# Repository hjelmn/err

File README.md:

This project contains all the files from my recreation of the Err LED sign. Included
in this repository are the current Kicad files.

The board is roughly based on the data available at:

https://hackaday.io/project/183827-reverse-engineering-the-mooninite-led-panels/details

with minor modifications (there could be errors-- if you find some please post a
PR with the fix):

 - Added a tactile switch to control the mode of the panel. The modes are off,
   light triggered, and various dimmed states but this can be changed by
   modifying the PIC firmware.
 - Added a barrel power input to support an external power supply. Added a
   circuit to disable the batter if an external power supply is connected. This
   circuit uses a P-channel MOSFET which closes the Batt+ when a voltage is
   detected on Vcc.
 - Added a battery pack connector and pads to solder on a battery.
 - Increased the LED driver voltage from 12v to 24v using boost regulator.
 - Changed the 5v regulator to a D2Pak style from the TO-220.
 - Added a 24 channel dimmable LED driver and rewired LEDs in chains of 6-8.
 - Changed to PIC16 to get I2C support but that is not needed with the LED
   controller chosen. It uses PWR so the originsl PIC12 is likely sufficient.

TODO:

 - Code for the microcontroller. Waiting on getting the parts before the code is
   finished.

The current version of the board costs roughly $85 to produce with LEDs from
China and parts sourced from the US.

To use this project download kicad and open the project.

The license for all of these files is GPLv3.

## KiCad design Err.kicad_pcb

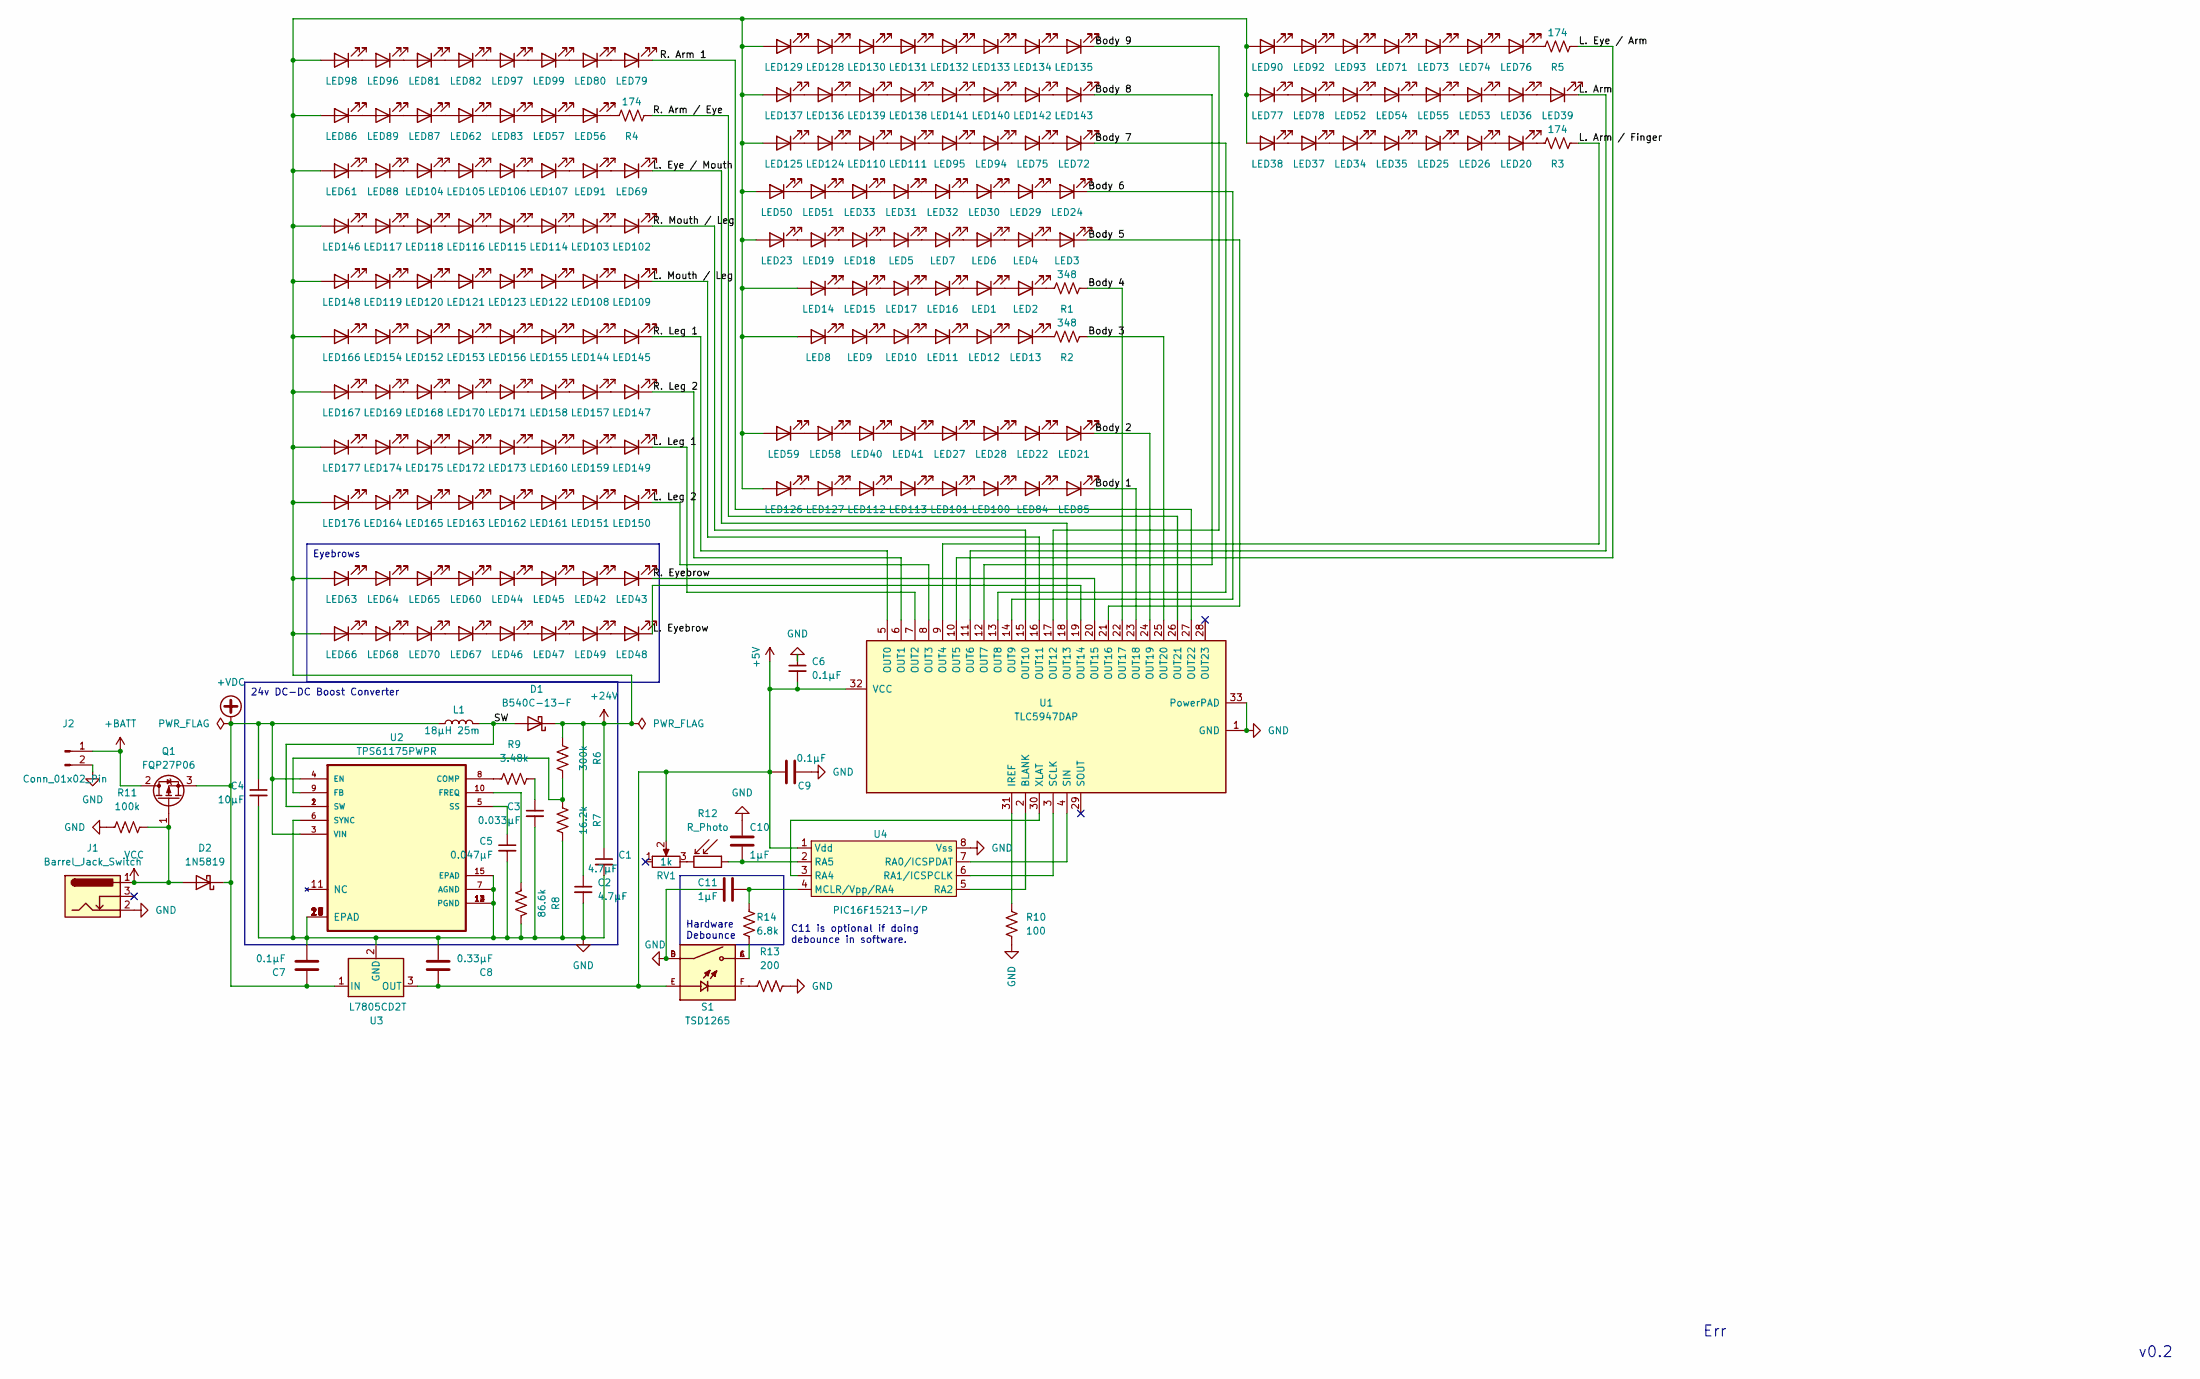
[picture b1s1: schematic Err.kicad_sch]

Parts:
C1, C2: 4.7µF; C_1206_3216Metric_Pad1.33x1.80mm_HandSolder; Part GRM31CR71H475KA12L
C3: 0.033µF; C_0805_2012Metric_Pad1.18x1.45mm_HandSolder; Part CGA4J2C0G1H333J125AA
C4: 10µF; C_1206_3216Metric_Pad1.33x1.80mm_HandSolder; Part GRM31CR71E106KA12L
C5: 0.047µF; C_0805_2012Metric_Pad1.18x1.45mm_HandSolder; Part C0805C473J3GACTU
C6: 0.1µF; C_0805_2012Metric_Pad1.18x1.45mm_HandSolder; Part GRM31CR71H475KA12L
C7, C9: 0.1µF; C_Disc_D3.0mm_W2.0mm_P2.50mm; Part C320C104K5R5TA
C8: 0.33µF; C_Disc_D5.1mm_W3.2mm_P5.00mm; Part SR215E334MAATR1
C10, C11: 1µF; C_Disc_D5.1mm_W3.2mm_P5.00mm; Part C330C105K5R5TA7301
D1: B540C-13-F; D_SMC-RM10_Universal_Handsoldering; Part B540C-13-F
D2: 1N5819; D_DO-41_SOD81_P10.16mm_Horizontal; Part 1N5819
J1: Barrel_Jack_Switch; BarrelJack_Wuerth_6941xx301002; Part SparkFun PRT-00119
J2: Conn_01x02_Pin; JST_EH_B2B-EH-A_1x02_P2.50mm_Vertical; Part B2B-XH-A
L1: 18µH 25m; IND_SRR1208-120ML; Part SRR1208-180ML
LED1, LED2, LED3, LED4, LED5, LED6, LED7, LED8, LED9, LED10, LED11, LED12, LED13, LED14, LED15, LED16, LED17, LED18, LED19, LED21, LED22, LED23, LED24, LED27, LED28, LED29, LED30, LED31, LED32, LED33, LED40, LED41, LED50, LED51, LED58, LED59, LED72, LED75, LED84, LED85, LED94, LED95, LED100, LED101, LED110, LED111, LED112, LED113, LED124, LED125, LED126, LED127, LED128, LED129, LED130, LED131, LED132, LED133, LED134, LED135, LED136, LED137, LED138, LED139, LED140, LED141, LED142, LED143: LED; LED_D10.0mm; Part 10mm Pink LED
LED20, LED25, LED26, LED34, LED35, LED36, LED37, LED38, LED39, LED42, LED43, LED44, LED45, LED46, LED47, LED48, LED49, LED52, LED53, LED54, LED55, LED56, LED57, LED60, LED61, LED62, LED63, LED64, LED65, LED66, LED67, LED68, LED69, LED70, LED71, LED73, LED74, LED76, LED77, LED78, LED79, LED80, LED81, LED82, LED83, LED86, LED87, LED88, LED89, LED90, LED91, LED92, LED93, LED96, LED97, LED98, LED99, LED102, LED103, LED104, LED105, LED106, LED107, LED108, LED109, LED114, LED115, LED116, LED117, LED118, LED119, LED120, LED121, LED122, LED123, LED144, LED145, LED146, LED147, LED148, LED149, LED150, LED151, LED152, LED153, LED154, LED155, LED156, LED157, LED158, LED159, LED160, LED161, LED162, LED163, LED164, LED165, LED166, LED167, LED168, LED169, LED170, LED171, LED172, LED173, LED174, LED175, LED176, LED177: LED; LED_D10.0mm; Part 10mm Blue LED
Q1: FQP27P06; TO-220-3_Horizontal_TabDown; Part FQP27P06
R1, R2: 348; R_Axial_DIN0207_L6.3mm_D2.5mm_P10.16mm_Horizontal; Part MFR-25FBF52-348R
R3, R4, R5: 174; R_Axial_DIN0207_L6.3mm_D2.5mm_P10.16mm_Horizontal; Part MFR-25FRF52-174R
R6: 300k; R_0603_1608Metric_Pad0.98x0.95mm_HandSolder; Part RC0603FR-07300KL
R7: 16.2k; R_0402_1005Metric_Pad0.72x0.64mm_HandSolder; Part CRCW040216K2FKED
R8: 86.6k; R_0201_0603Metric_Pad0.64x0.40mm_HandSolder; Part RC0201FR-0786K6L
R9: 3.48k; R_0402_1005Metric_Pad0.72x0.64mm_HandSolder; Part CRCW04023K48FKED
R10: 100; R_0805_2012Metric_Pad1.20x1.40mm_HandSolder; Part ERJ-P06F1000V
R11: 100k; R_Axial_DIN0207_L6.3mm_D2.5mm_P10.16mm_Horizontal; Part MFR-25FRF52-100K
R12: R_Photo; R_LDR_D6.4mm_P3.4mm_Vertical; Part SparkFun SEN-09088
R13: 200; R_Axial_DIN0207_L6.3mm_D2.5mm_P10.16mm_Horizontal; Part MFR-25FRF52-200R
R14: 6.8k; R_Axial_DIN0207_L6.3mm_D2.5mm_P10.16mm_Horizontal; Part MFR-25FRF52-200R
RV1: 1k; Potentiometer_Bourns_3299W_Vertical; Part 3299W-1-103LF
S1: TSD1265; SW_TSD1265; PARTREV N/A
U1: TLC5947DAP; HTSSOP-32-1EP_6.1x11mm_P0.65mm_EP5.2x11mm_Mask4.11x4.36mm_T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; Part TLC5947DAP
U2: TPS61175PWPR; IC_TPS27S100BPWPR; Part TPS61175PWPR
U3: L7805CD2T; TO-263-2; Part L7805CD2T
U4: PIC16F15213-I/P; DIP-8_W7.62mm; Part PIC16F15213-I/P

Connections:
+5V: C6.2, C8.1, C9.2, RV1.2, S1.E, U1.32 (VCC), U3.3 (OUT), U4.1 (Vdd)
+24V: C1.1, C2.1, D1.1 (K), LED8.2 (A), LED14.2 (A), LED23.2 (A), LED38.2 (A), LED50.2 (A), LED59.2 (A), LED61.2 (A), LED63.2 (A), LED66.2 (A), LED77.2 (A), LED86.2 (A), LED90.2 (A), LED98.2 (A), LED125.2 (A), LED126.2 (A), LED129.2 (A), LED137.2 (A), LED146.2 (A), LED148.2 (A), LED166.2 (A), LED167.2 (A), LED176.2 (A), LED177.2 (A), R6.2
+BATT: J2.1, Q1.2 (D)
+VDC: C4.1, C7.2, D2.1 (K), L1.1, Q1.3 (S), U2.3 (VIN), U2.4 (EN), U3.1 (IN)
/Body 1: LED85.1 (K), U1.23 (OUT18)
/Body 2: LED21.1 (K), U1.24 (OUT19)
/Body 3: R2.2, U1.25 (OUT20)
/Body 4: R1.2, U1.22 (OUT17)
/Body 5: LED3.1 (K), U1.21 (OUT16)
/Body 6: LED24.1 (K), U1.14 (OUT9)
/Body 7: LED72.1 (K), U1.13 (OUT8)
/Body 8: LED143.1 (K), U1.12 (OUT7)
/Body 9: LED135.1 (K), U1.17 (OUT12)
/L. Arm: LED39.1 (K), U1.11 (OUT6)
/L. Arm / Finger: R3.2, U1.9 (OUT4)
/L. Eye / Arm: R5.1, U1.10 (OUT5)
/L. Eye / Mouth: LED69.1 (K), U1.18 (OUT13)
/L. Eyebrow: LED48.1 (K), U1.19 (OUT14)
/L. Leg 1: LED149.1 (K), U1.7 (OUT2)
/L. Leg 2: LED150.1 (K), U1.8 (OUT3)
/L. Mouth / Leg: LED109.1 (K), U1.16 (OUT11)
/R. Arm 1: LED79.1 (K), U1.27 (OUT22)
/R. Arm / Eye: R4.1, U1.26 (OUT21)
/R. Eyebrow: LED43.1 (K), U1.20 (OUT15)
/R. Leg 1: LED145.1 (K), U1.5 (OUT0)
/R. Leg 2: LED147.1 (K), U1.6 (OUT1)
/R. Mouth / Leg: LED102.1 (K), U1.15 (OUT10)
/SW: D1.2 (A), L1.2, U2.1 (SW), U2.2 (SW)
GND: C1.2, C2.2, C3.2, C4.2, C5.2, C6.1, C7.1, C8.2, C9.1, C10.1, C11.2, J1.2, J2.2, R7.1, R8.2, R10.1, R11.2, R13.1, S1.B, S1.D, U1.1 (GND), U1.33 (PowerPAD), U2.6 (SYNC), U2.7 (AGND), U2.12 (PGND), U2.13 (PGND), U2.14 (PGND), U2.15 (EPAD), U2.16 (EPAD), U2.17 (EPAD), U2.18 (EPAD), U2.19 (EPAD), U2.20 (EPAD), U2.21 (EPAD), U3.2 (GND), U4.8 (Vss)
unnamed: C3.1, R9.1
unnamed: LED1.2 (A), LED16.1 (K)
unnamed: LED1.1 (K), LED2.2 (A)
unnamed: LED2.1 (K), R1.1
unnamed: LED3.2 (A), LED4.1 (K)
unnamed: LED4.2 (A), LED6.1 (K)
unnamed: LED5.1 (K), LED7.2 (A)
unnamed: LED6.2 (A), LED7.1 (K)
unnamed: LED8.1 (K), LED9.2 (A)
unnamed: LED9.1 (K), LED10.2 (A)
unnamed: LED10.1 (K), LED11.2 (A)
unnamed: LED11.1 (K), LED12.2 (A)
unnamed: LED12.1 (K), LED13.2 (A)
unnamed: LED13.1 (K), R2.1
unnamed: LED14.1 (K), LED15.2 (A)
unnamed: LED15.1 (K), LED17.2 (A)
unnamed: LED16.2 (A), LED17.1 (K)
unnamed: LED18.2 (A), LED19.1 (K)
unnamed: LED5.2 (A), LED18.1 (K)
unnamed: LED19.2 (A), LED23.1 (K)
unnamed: LED20.2 (A), LED26.1 (K)
unnamed: LED20.1 (K), R3.1
unnamed: LED21.2 (A), LED22.1 (K)
unnamed: LED22.2 (A), LED28.1 (K)
unnamed: LED24.2 (A), LED29.1 (K)
unnamed: LED25.2 (A), LED35.1 (K)
unnamed: LED25.1 (K), LED26.2 (A)
unnamed: LED27.2 (A), LED41.1 (K)
unnamed: LED27.1 (K), LED28.2 (A)
unnamed: LED29.2 (A), LED30.1 (K)
unnamed: LED30.2 (A), LED32.1 (K)
unnamed: LED31.2 (A), LED33.1 (K)
unnamed: LED31.1 (K), LED32.2 (A)
unnamed: LED33.2 (A), LED51.1 (K)
unnamed: LED34.2 (A), LED37.1 (K)
unnamed: LED34.1 (K), LED35.2 (A)
unnamed: LED36.2 (A), LED53.1 (K)
unnamed: LED36.1 (K), LED39.2 (A)
unnamed: LED37.2 (A), LED38.1 (K)
unnamed: LED40.2 (A), LED58.1 (K)
unnamed: LED40.1 (K), LED41.2 (A)
unnamed: LED42.2 (A), LED45.1 (K)
unnamed: LED42.1 (K), LED43.2 (A)
unnamed: LED44.2 (A), LED60.1 (K)
unnamed: LED44.1 (K), LED45.2 (A)
unnamed: LED46.2 (A), LED67.1 (K)
unnamed: LED46.1 (K), LED47.2 (A)
unnamed: LED47.1 (K), LED49.2 (A)
unnamed: LED48.2 (A), LED49.1 (K)
unnamed: LED50.1 (K), LED51.2 (A)
unnamed: LED52.2 (A), LED78.1 (K)
unnamed: LED52.1 (K), LED54.2 (A)
unnamed: LED53.2 (A), LED55.1 (K)
unnamed: LED54.1 (K), LED55.2 (A)
unnamed: LED56.2 (A), LED57.1 (K)
unnamed: LED56.1 (K), R4.2
unnamed: LED57.2 (A), LED83.1 (K)
unnamed: LED58.2 (A), LED59.1 (K)
unnamed: LED60.2 (A), LED65.1 (K)
unnamed: LED61.1 (K), LED88.2 (A)
unnamed: LED62.2 (A), LED87.1 (K)
unnamed: LED62.1 (K), LED83.2 (A)
unnamed: LED63.1 (K), LED64.2 (A)
unnamed: LED64.1 (K), LED65.2 (A)
unnamed: LED66.1 (K), LED68.2 (A)
unnamed: LED67.2 (A), LED70.1 (K)
unnamed: LED68.1 (K), LED70.2 (A)
unnamed: LED69.2 (A), LED91.1 (K)
unnamed: LED71.2 (A), LED93.1 (K)
unnamed: LED71.1 (K), LED73.2 (A)
unnamed: LED72.2 (A), LED75.1 (K)
unnamed: LED73.1 (K), LED74.2 (A)
unnamed: LED74.1 (K), LED76.2 (A)
unnamed: LED75.2 (A), LED94.1 (K)
unnamed: LED76.1 (K), R5.2
unnamed: LED77.1 (K), LED78.2 (A)
unnamed: LED79.2 (A), LED80.1 (K)
unnamed: LED80.2 (A), LED99.1 (K)
unnamed: LED81.2 (A), LED96.1 (K)
unnamed: LED81.1 (K), LED82.2 (A)
unnamed: LED82.1 (K), LED97.2 (A)
unnamed: LED84.1 (K), LED85.2 (A)
unnamed: LED86.1 (K), LED89.2 (A)
unnamed: LED87.2 (A), LED89.1 (K)
unnamed: LED90.1 (K), LED92.2 (A)
unnamed: LED92.1 (K), LED93.2 (A)
unnamed: LED94.2 (A), LED95.1 (K)
unnamed: LED96.2 (A), LED98.1 (K)
unnamed: LED97.1 (K), LED99.2 (A)
unnamed: LED100.2 (A), LED101.1 (K)
unnamed: LED84.2 (A), LED100.1 (K)
unnamed: LED101.2 (A), LED113.1 (K)
unnamed: LED102.2 (A), LED103.1 (K)
unnamed: LED103.2 (A), LED114.1 (K)
unnamed: LED88.1 (K), LED104.2 (A)
unnamed: LED104.1 (K), LED105.2 (A)
unnamed: LED105.1 (K), LED106.2 (A)
unnamed: LED106.1 (K), LED107.2 (A)
unnamed: LED91.2 (A), LED107.1 (K)
unnamed: LED108.2 (A), LED122.1 (K)
unnamed: LED108.1 (K), LED109.2 (A)
unnamed: LED110.2 (A), LED124.1 (K)
unnamed: LED110.1 (K), LED111.2 (A)
unnamed: LED95.2 (A), LED111.1 (K)
unnamed: LED112.2 (A), LED127.1 (K)
unnamed: LED112.1 (K), LED113.2 (A)
unnamed: LED114.2 (A), LED115.1 (K)
unnamed: LED115.2 (A), LED116.1 (K)
unnamed: LED116.2 (A), LED118.1 (K)
unnamed: LED117.2 (A), LED146.1 (K)
unnamed: LED117.1 (K), LED118.2 (A)
unnamed: LED119.2 (A), LED148.1 (K)
unnamed: LED119.1 (K), LED120.2 (A)
unnamed: LED120.1 (K), LED121.2 (A)
unnamed: LED121.1 (K), LED123.2 (A)
unnamed: LED122.2 (A), LED123.1 (K)
unnamed: LED124.2 (A), LED125.1 (K)
unnamed: LED126.1 (K), LED127.2 (A)
unnamed: LED128.2 (A), LED129.1 (K)
unnamed: LED128.1 (K), LED130.2 (A)
unnamed: LED130.1 (K), LED131.2 (A)
unnamed: LED131.1 (K), LED132.2 (A)
unnamed: LED132.1 (K), LED133.2 (A)
unnamed: LED133.1 (K), LED134.2 (A)
unnamed: LED134.1 (K), LED135.2 (A)
unnamed: LED136.2 (A), LED137.1 (K)
unnamed: LED136.1 (K), LED139.2 (A)
unnamed: LED138.2 (A), LED139.1 (K)
unnamed: LED138.1 (K), LED141.2 (A)
unnamed: LED140.2 (A), LED141.1 (K)
unnamed: LED140.1 (K), LED142.2 (A)
unnamed: LED142.1 (K), LED143.2 (A)
unnamed: LED144.2 (A), LED155.1 (K)
unnamed: LED144.1 (K), LED145.2 (A)
unnamed: LED147.2 (A), LED157.1 (K)
unnamed: LED149.2 (A), LED159.1 (K)
unnamed: LED150.2 (A), LED151.1 (K)
unnamed: LED151.2 (A), LED161.1 (K)
unnamed: LED152.2 (A), LED154.1 (K)
unnamed: LED152.1 (K), LED153.2 (A)
unnamed: LED153.1 (K), LED156.2 (A)
unnamed: LED154.2 (A), LED166.1 (K)
unnamed: LED155.2 (A), LED156.1 (K)
unnamed: LED157.2 (A), LED158.1 (K)
unnamed: LED158.2 (A), LED171.1 (K)
unnamed: LED159.2 (A), LED160.1 (K)
unnamed: LED160.2 (A), LED173.1 (K)
unnamed: LED161.2 (A), LED162.1 (K)
unnamed: LED162.2 (A), LED163.1 (K)
unnamed: LED163.2 (A), LED165.1 (K)
unnamed: LED164.2 (A), LED176.1 (K)
unnamed: LED164.1 (K), LED165.2 (A)
unnamed: LED167.1 (K), LED169.2 (A)
unnamed: LED168.2 (A), LED169.1 (K)
unnamed: LED168.1 (K), LED170.2 (A)
unnamed: LED170.1 (K), LED171.2 (A)
unnamed: LED172.2 (A), LED175.1 (K)
unnamed: LED172.1 (K), LED173.2 (A)
unnamed: LED174.2 (A), LED177.1 (K)
unnamed: LED174.1 (K), LED175.2 (A)
unnamed: R12.2, RV1.3
unnamed: R13.2, S1.F
unnamed: R14.1, S1.A, S1.C
unnamed: U1.2 (BLANK), U4.5 (RA2)
unnamed: R10.2, U1.31 (IREF)
unnamed: U1.3 (SCLK), U4.6 (RA1/ICSPCLK)
unnamed: U1.4 (SIN), U4.7 (RA0/ICSPDAT)
unnamed: U1.30 (XLAT), U4.3 (RA4)
unnamed: R9.2, U2.8 (COMP)
unnamed: R6.1, R7.2, U2.9 (FB)
unnamed: R8.1, U2.10 (FREQ)
unnamed: C5.1, U2.5 (SS)
unnamed: C11.1, R14.2, U4.4 (MCLR/Vpp/RA4)
unnamed: C10.2, R12.1, U4.2 (RA5)
VCC: D2.2 (A), J1.1, Q1.1 (G), R11.1

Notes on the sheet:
Hardware Debounce
Eyebrows
24v DC-DC Boost Converter
C11 is optional if doing debounce in software.
v0.2
Err

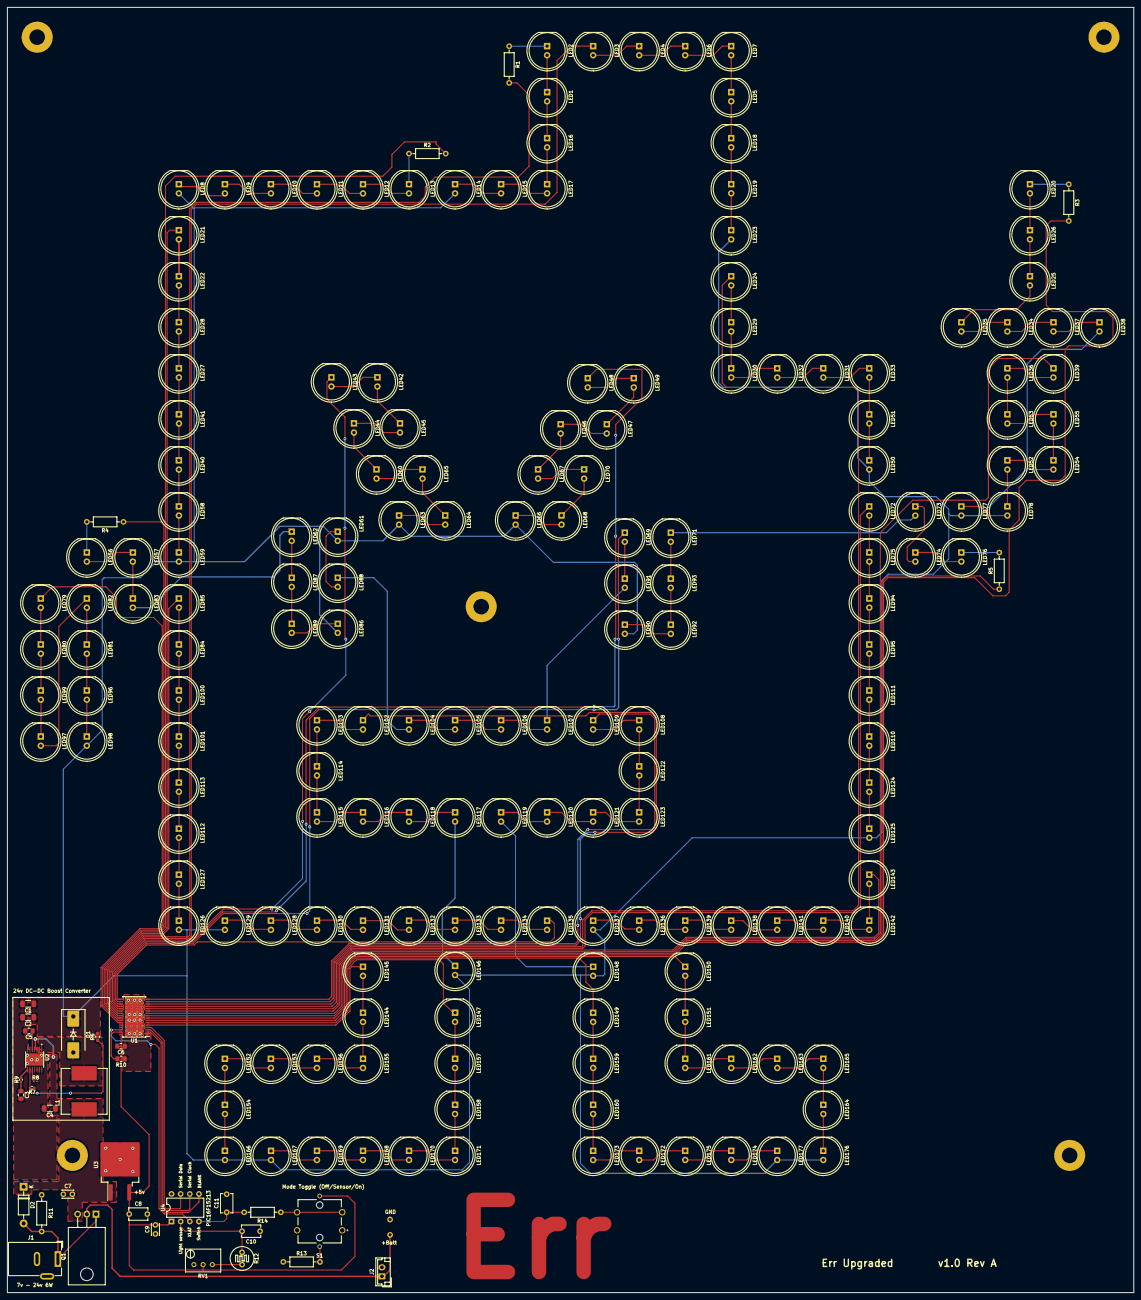
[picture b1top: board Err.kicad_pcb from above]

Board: 2 copper layers, 312.0 x 356.0 mm, 214 parts (0 on the bottom side), 204 nets.

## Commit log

2024-03-17 Initial version of err
    This design deviates from the original in multiple way. Fist, it uses either a battery input or a barrel power input. Second, it uses 24v instead of the original 12v. And, finally, it uses a dedicate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
